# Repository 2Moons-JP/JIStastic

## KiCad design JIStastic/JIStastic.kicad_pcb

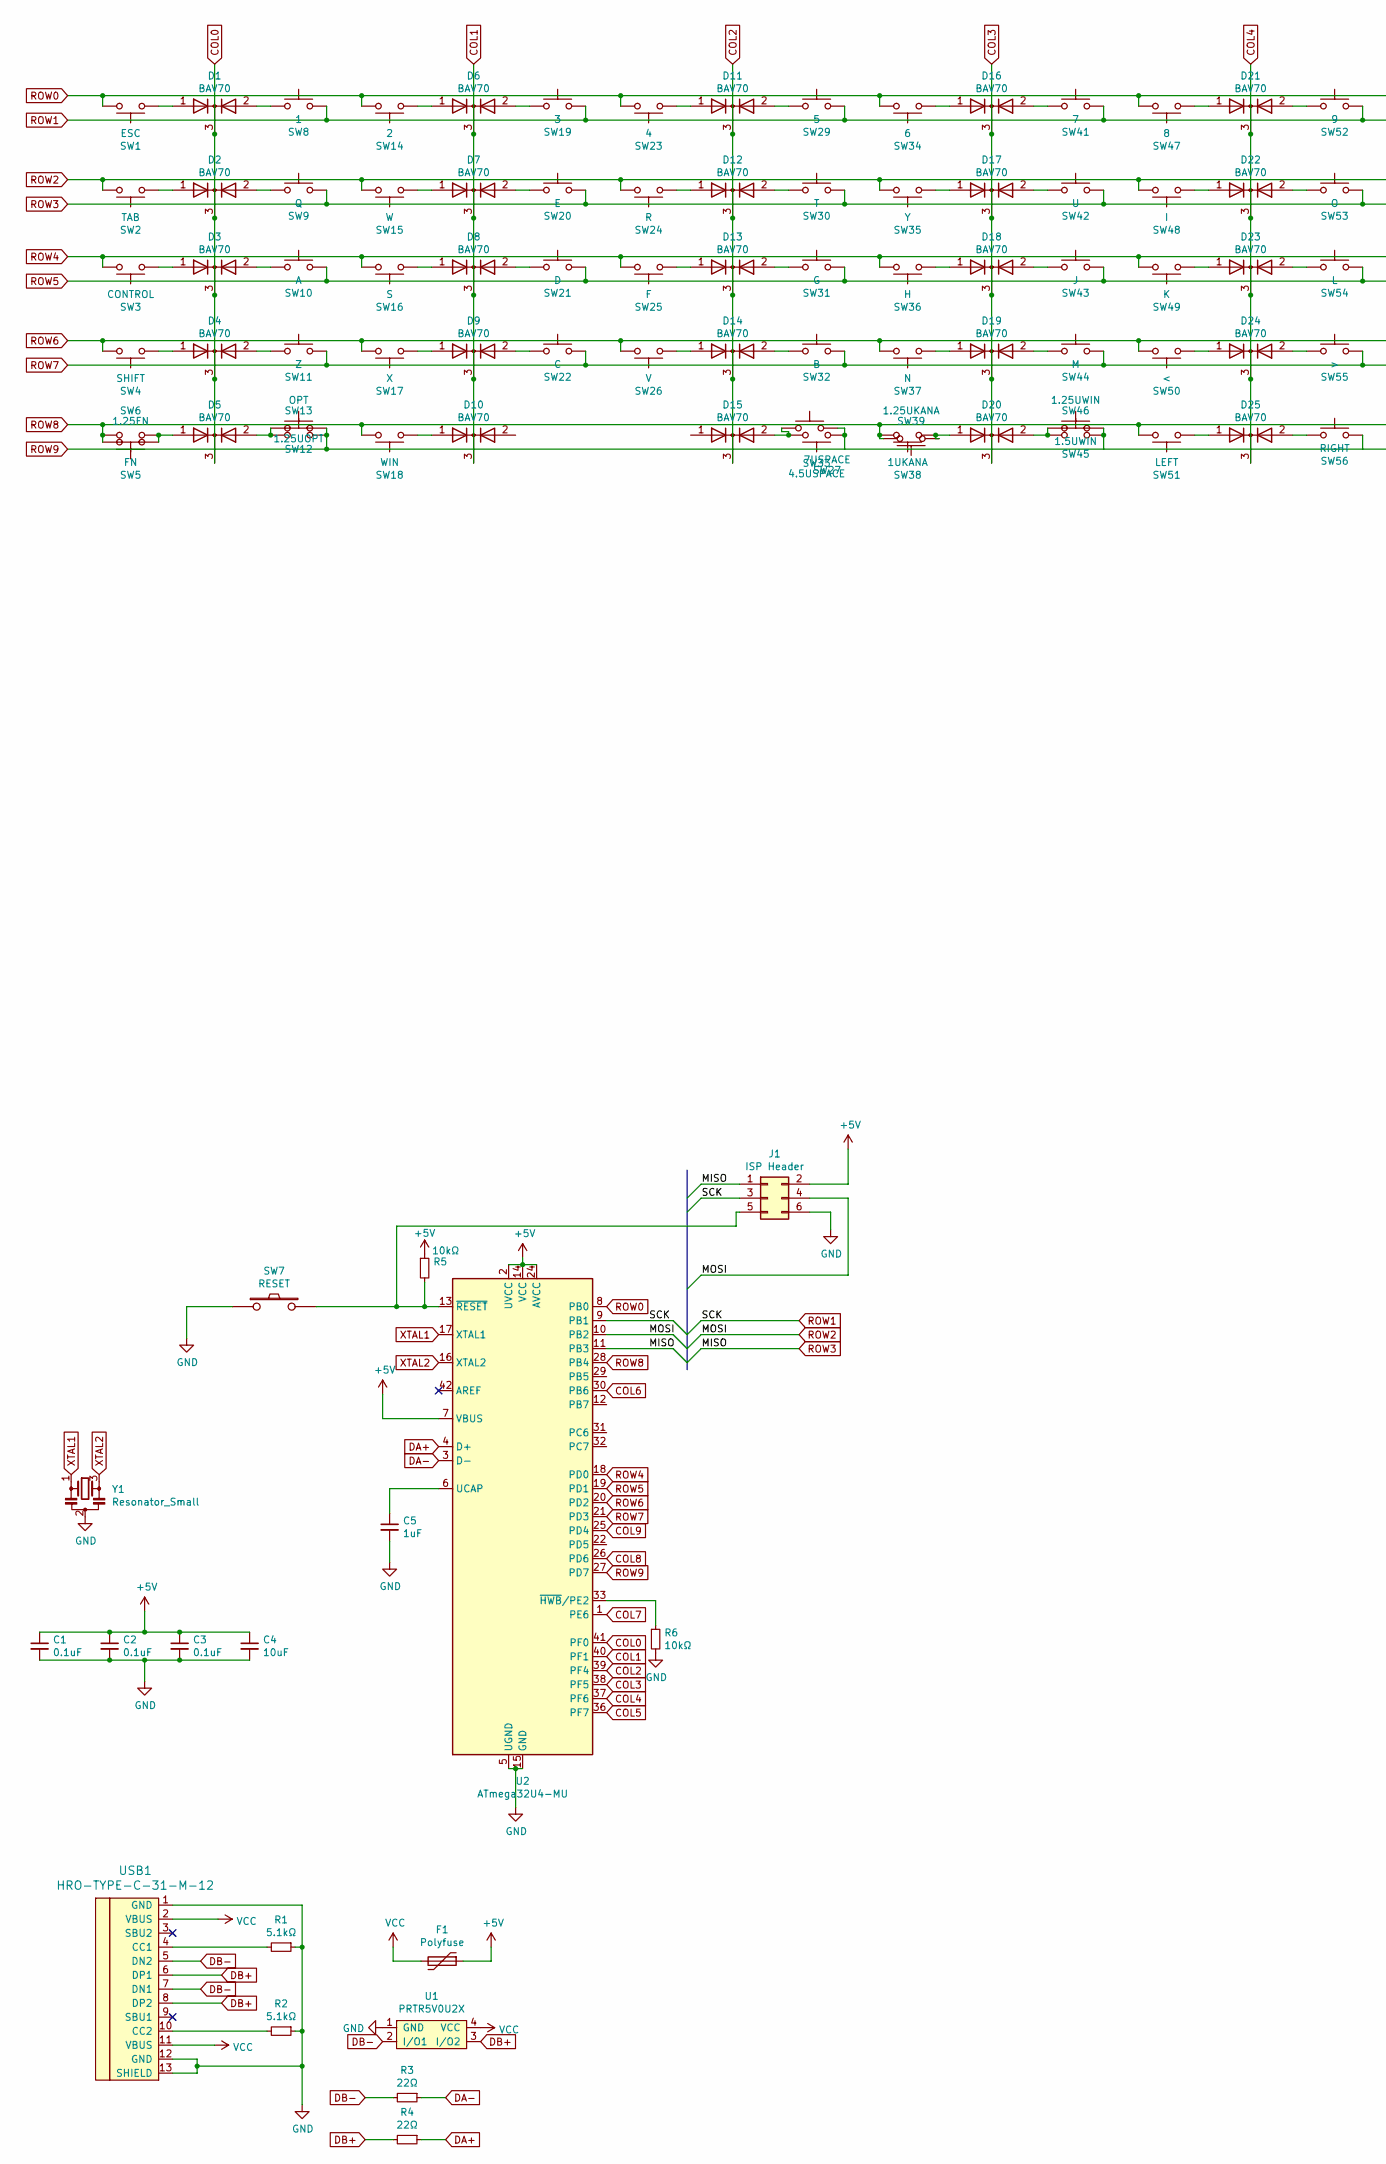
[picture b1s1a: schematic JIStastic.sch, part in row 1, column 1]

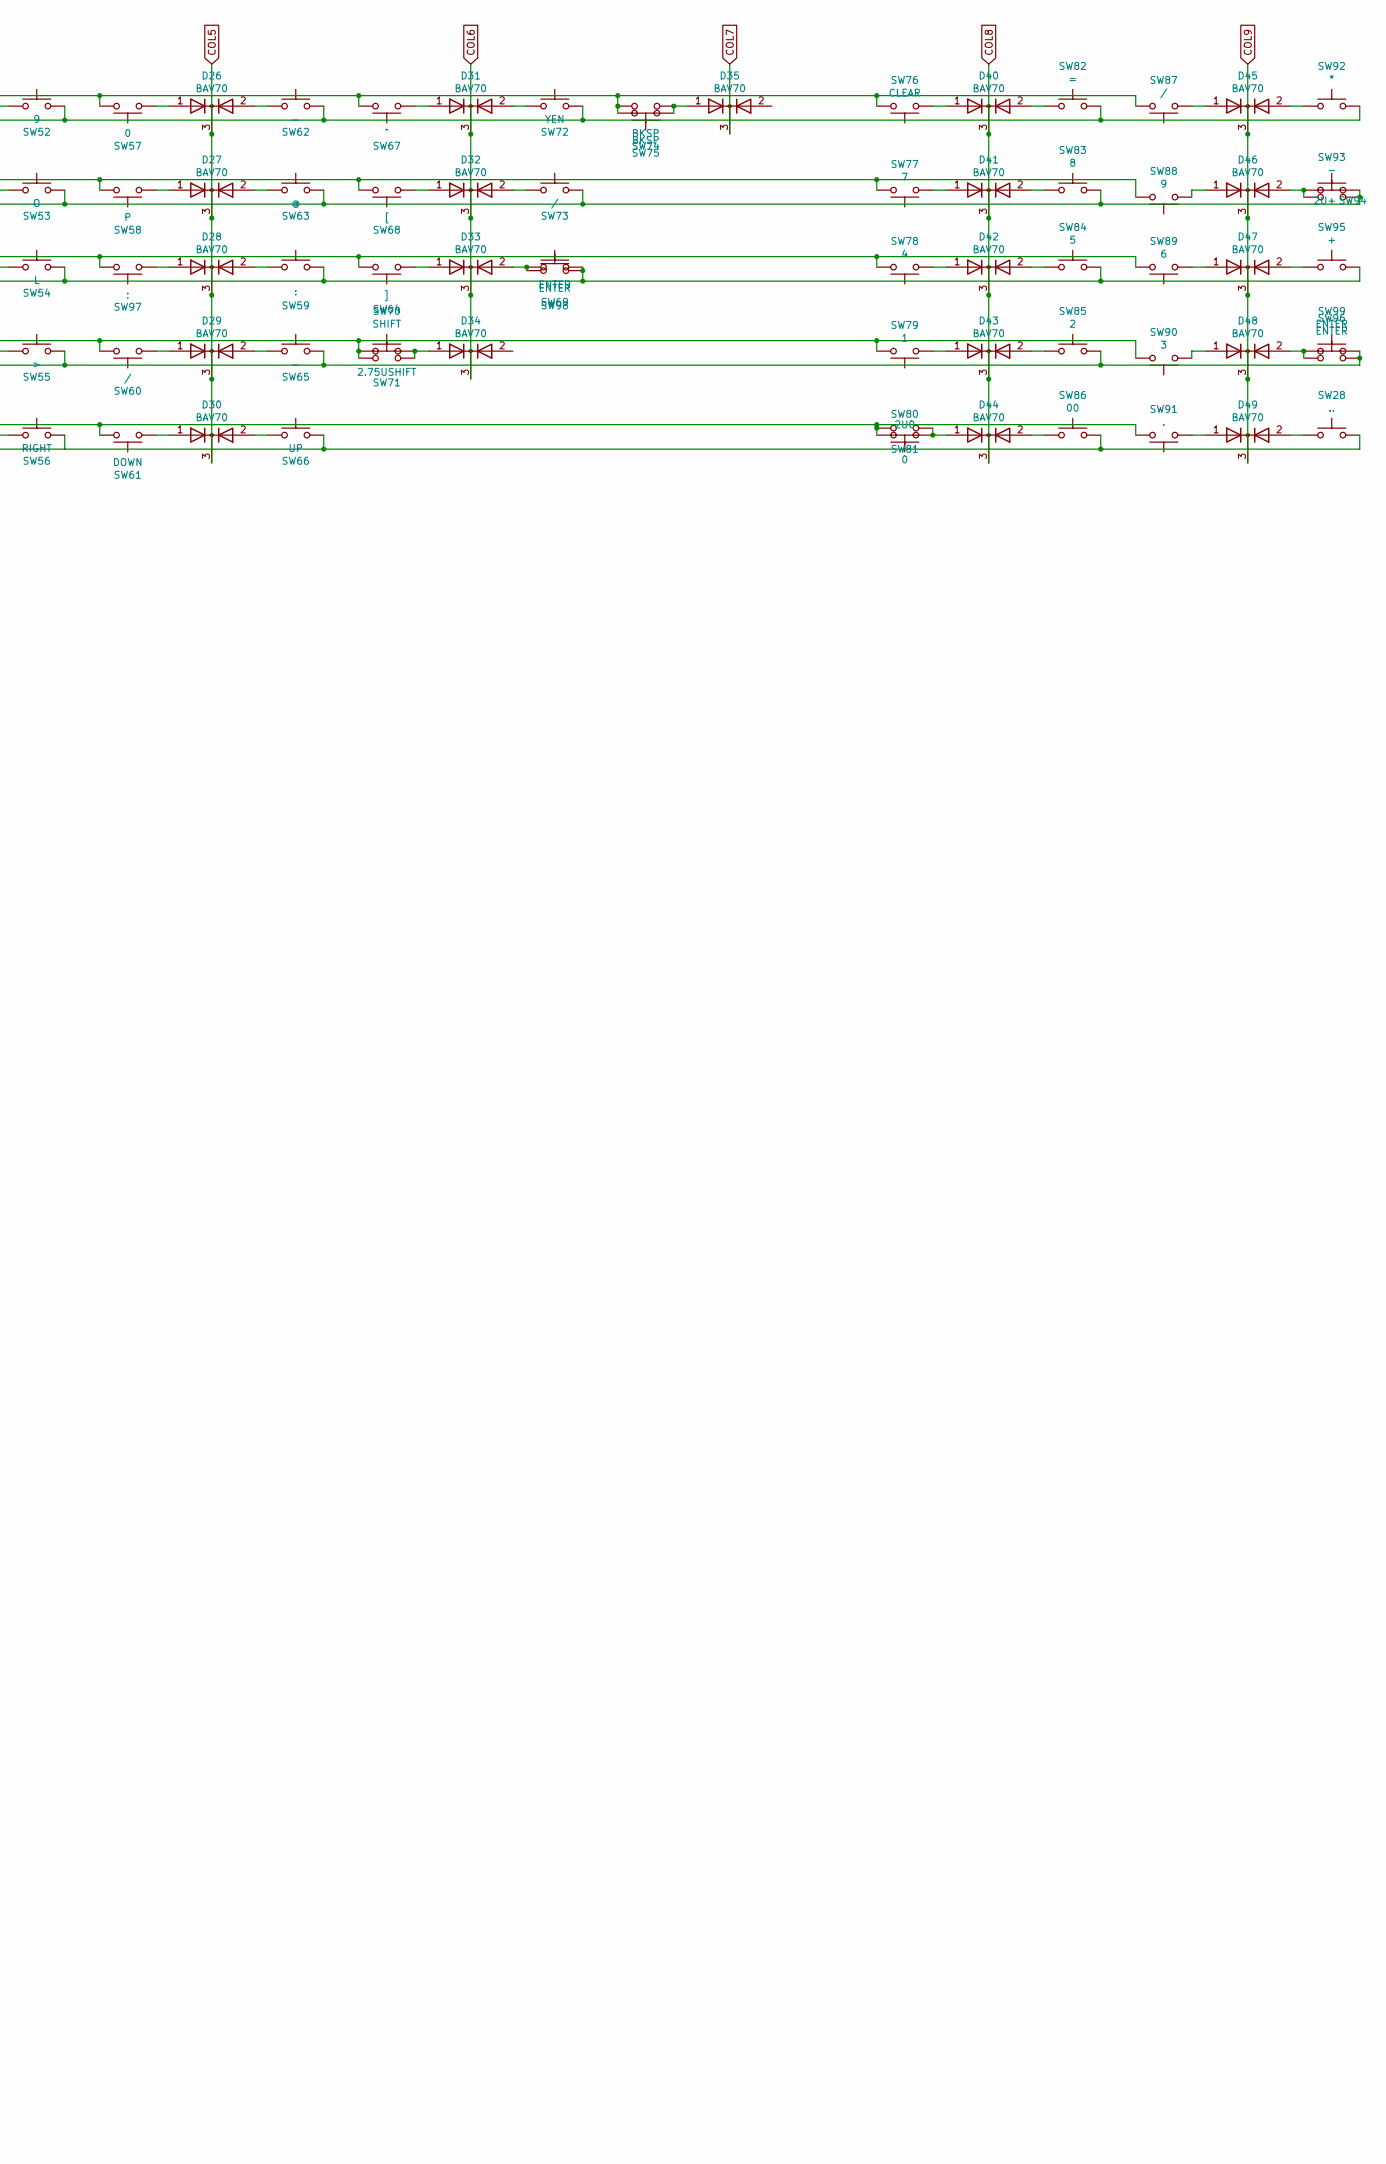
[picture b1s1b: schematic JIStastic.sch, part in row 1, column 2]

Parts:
C1, C2, C3: 0.1uF; C_0805_2012Metric; Part# CC0805KRX7R9BB104; LCSC Part# C49678
C4: 10uF; C_0805_2012Metric; Part# CL21A106KAYNNNE; LCSC Part# C15850
C5: 1uF; C_0805_2012Metric; Part# CL21B105KBFNNNE; LCSC Part# C28323
D1, D2, D3, D4, D5, D6, D7, D8, D9, D10, D11, D12, D13, D14, D15, D16, D17, D18, D19, D20, D21, D22, D23, D24, D25, D26, D27, D28, D29, D30, D31, D32, D33, D34, D35, D40, D41, D42, D43, D44, D45, D46, D47, D48, D49: BAV70; SOT-23; Part# BAV70; LCSC Part# C68978
F1: Polyfuse; Fuse_0805_2012Metric; Part# nSMD025; LCSC Part# C70068
J1: ISP Header; PinHeader_2x03_P2.54mm_Vertical
R1, R2: 5.1kΩ; R_0805_2012Metric; Part# 0805W8F5101T5E; LCSC Part# C27834
R3, R4: 22Ω; R_0805_2012Metric; Part# 0805W8F220JT5E; LCSC Part# C17561
R5, R6: 10kΩ; R_0805_2012Metric; Part# 0805W8F1002T5E; LCSC Part# C17414
SW1: ESC; MXOnly-1U-NoLED
SW2: TAB; MXOnly-1.5U-NoLED
SW3: CONTROL; MXOnly-1.75U-NoLED
SW4: SHIFT; MXOnly-2.25U-NoLED
SW5: FN; MXOnly-1U-NoLED
SW6: 1.25FN; MXOnly-1.25U-NoLED
SW7: RESET; SKQG-1155865; LCSC Part# C221929
SW8, SW79: 1; MXOnly-1U-NoLED
SW9: Q; MXOnly-1U-NoLED
SW10: A; MXOnly-1U-NoLED
SW11: Z; MXOnly-1U-NoLED
SW12: 1.25UOPT; MXOnly-1.25U-NoLED
SW13: OPT; MXOnly-1.5U-NoLED
SW14, SW85: 2; MXOnly-1U-NoLED
SW15: W; MXOnly-1U-NoLED
SW16: S; MXOnly-1U-NoLED
SW17: X; MXOnly-1U-NoLED
SW18: WIN; MXOnly-1.5U-NoLED
SW19, SW90: 3; MXOnly-1U-NoLED
SW20: E; MXOnly-1U-NoLED
SW21: D; MXOnly-1U-NoLED
SW22: C; MXOnly-1U-NoLED
SW23, SW78: 4; MXOnly-1U-NoLED
SW24: R; MXOnly-1U-NoLED
SW25: F; MXOnly-1U-NoLED
SW26: V; MXOnly-1U-NoLED
SW27: 7USPACE; MXOnly-7U-ReversedStabilizers-NoLED
SW28: ..; MXOnly-1U-NoLED
SW29, SW84: 5; MXOnly-1U-NoLED
SW30: T; MXOnly-1U-NoLED
SW31: G; MXOnly-1U-NoLED
SW32: B; MXOnly-1U-NoLED
SW33: 4.5USPACE; MX450R
SW34, SW89: 6; MXOnly-1U-NoLED
SW35: Y; MXOnly-1U-NoLED
SW36: H; MXOnly-1U-NoLED
SW37: N; MXOnly-1U-NoLED
SW38: 1UKANA; MXOnly-1U-NoLED
SW39: 1.25UKANA; MXOnly-1.25U-NoLED
SW41, SW77: 7; MXOnly-1U-NoLED
SW42: U; MXOnly-1U-NoLED
SW43: J; MXOnly-1U-NoLED
SW44: M; MXOnly-1U-NoLED
SW45: 1.5UWIN; MXOnly-1.5U-NoLED
SW46: 1.25UWIN; MXOnly-1.25U-NoLED
SW47, SW83: 8; MXOnly-1U-NoLED
SW48: I; MXOnly-1U-NoLED
SW49: K; MXOnly-1U-NoLED
SW50: <; MXOnly-1U-NoLED
SW51: LEFT; MXOnly-1U-NoLED
SW52, SW88: 9; MXOnly-1U-NoLED
SW53: O; MXOnly-1U-NoLED
SW54: L; MXOnly-1U-NoLED
SW55: >; MXOnly-1U-NoLED
SW56: RIGHT; MXOnly-1U-NoLED
SW57, SW81: 0; MXOnly-1U-NoLED
SW58: P; MXOnly-1U-NoLED
SW59: :; MXOnly-1U-NoLED
SW60, SW87: /; MXOnly-1U-NoLED
SW61: DOWN; MXOnly-1U-NoLED
SW62, SW65, SW93: -; MXOnly-1U-NoLED
SW63: @; MXOnly-1U-NoLED
SW64: ]; MXOnly-1U-NoLED
SW66: UP; MXOnly-1U-NoLED
SW67: ^; MXOnly-1U-NoLED
SW68: [; MXOnly-1U-NoLED
SW69: ENTER; MXOnly-ISO-ROTATED-ReversedStabilizers-NoLED
SW70: SHIFT; MXOnly-1.75U-NoLED
SW71: 2.75USHIFT; MXOnly-2.75U-NoLED
SW72: YEN; MXOnly-1U-NoLED
SW73: /; MXOnly-1.5U-NoLED
SW74: BKSP; MXOnly-2U-NoLED
SW75: BKSP; MXOnly-1U-NoLED
SW76: CLEAR; MXOnly-1U-NoLED
SW80: 2U0; MXOnly-2U-ReversedStabilizers-NoLED
SW82: =; MXOnly-1U-NoLED
SW86: 00; MXOnly-1U-NoLED
SW91: .; MXOnly-1U-NoLED
SW92: *; MXOnly-1U-NoLED
SW94: 2U+; MXOnly-2U-ReversedStabilizers-NoLED
SW95: +; MXOnly-1U-NoLED
SW96: ENTER; MXOnly-2U-ReversedStabilizers-NoLED
SW97: ;; MXOnly-1U-NoLED
SW98: ENTER; MXOnly-2.25U-NoLED
SW99: ENTER; MXOnly-1U-NoLED
U1: PRTR5V0U2X; SOT-143
U2: ATmega32U4-MU; QFN-44-1EP_7x7mm_P0.5mm_EP5.2x5.2mm; Part# ATMEGA32U4-MUR; LCSC Part# C45874
USB1: HRO-TYPE-C-31-M-12; HRO-TYPE-C-31-M-12-Assembly; Part# TYPE-C-31-M-12; LCSC Part# C165948
Y1: Resonator_Small; Resonator_SMD_muRata_CSTxExxV-3Pin_3.0x1.1mm_HandSoldering_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; Part# CSTNE16M0V530000R0; LCSC Part# C341521

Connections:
+5V: C1.1, C2.1, C3.1, C4.1, F1.1, J1.2, R5.1, U2.2 (UVCC), U2.7 (VBUS), U2.14 (VCC), U2.24 (AVCC), U2.34 (VCC), U2.44 (AVCC)
COL0: D1.3 (K), D2.3 (K), D3.3 (K), D4.3 (K), D5.3 (K), U2.41 (PF0)
COL1: D6.3 (K), D7.3 (K), D8.3 (K), D9.3 (K), D10.3 (K), U2.40 (PF1)
COL2: D11.3 (K), D12.3 (K), D13.3 (K), D14.3 (K), D15.3 (K), U2.39 (PF4)
COL3: D16.3 (K), D17.3 (K), D18.3 (K), D19.3 (K), D20.3 (K), U2.38 (PF5)
COL4: D21.3 (K), D22.3 (K), D23.3 (K), D24.3 (K), D25.3 (K), U2.37 (PF6)
COL5: D26.3 (K), D27.3 (K), D28.3 (K), D29.3 (K), D30.3 (K), U2.36 (PF7)
COL6: D31.3 (K), D32.3 (K), D33.3 (K), D34.3 (K), U2.30 (PB6)
COL7: D35.3 (K), U2.1 (PE6)
COL8: D40.3 (K), D41.3 (K), D42.3 (K), D43.3 (K), D44.3 (K), U2.26 (PD6)
COL9: D45.3 (K), D46.3 (K), D47.3 (K), D48.3 (K), D49.3 (K), U2.25 (PD4)
DA+: R4.1, U2.4 (D+)
DA-: R3.1, U2.3 (D-)
DB+: R4.2, U1.3 (I/O2), USB1.6 (DP1), USB1.8 (DP2)
DB-: R3.2, U1.2 (I/O1), USB1.5 (DN2), USB1.7 (DN1)
GND: C1.2, C2.2, C3.2, C4.2, C5.2, J1.6, R1.1, R2.1, R6.2, SW7.1, U1.1 (GND), U2.5 (UGND), U2.15 (GND), U2.23 (GND), U2.35 (GND), U2.43 (GND), U2.45 (GND), USB1.1 (GND), USB1.12 (GND), USB1.13 (SHIELD), Y1.2
unnamed: C5.1, U2.6 (UCAP)
unnamed: D1.1 (A), SW1.1
unnamed: D1.2 (A), SW8.1
unnamed: D2.1 (A), SW2.1
unnamed: D2.2 (A), SW9.1
unnamed: D3.1 (A), SW3.1
unnamed: D3.2 (A), SW10.1
unnamed: D4.1 (A), SW4.1
unnamed: D4.2 (A), SW11.1
unnamed: D5.1 (A), SW5.1, SW6.1
unnamed: D5.2 (A), SW12.1, SW13.1
unnamed: D6.1 (A), SW14.1
unnamed: D6.2 (A), SW19.1
unnamed: D7.1 (A), SW15.1
unnamed: D7.2 (A), SW20.1
unnamed: D8.1 (A), SW16.1
unnamed: D8.2 (A), SW21.1
unnamed: D9.1 (A), SW17.1
unnamed: D9.2 (A), SW22.1
unnamed: D10.1 (A), SW18.1
unnamed: D11.1 (A), SW23.1
unnamed: D11.2 (A), SW29.1
unnamed: D12.1 (A), SW24.1
unnamed: D12.2 (A), SW30.1
unnamed: D13.1 (A), SW25.1
unnamed: D13.2 (A), SW31.1
unnamed: D14.1 (A), SW26.1
unnamed: D14.2 (A), SW32.1
unnamed: D15.2 (A), SW27.1, SW33.2
unnamed: D16.1 (A), SW34.1
unnamed: D16.2 (A), SW41.1
unnamed: D17.1 (A), SW35.1
unnamed: D17.2 (A), SW42.1
unnamed: D18.1 (A), SW36.1
unnamed: D18.2 (A), SW43.1
unnamed: D19.1 (A), SW37.1
unnamed: D19.2 (A), SW44.1
unnamed: D20.1 (A), SW38.1, SW39.1
unnamed: D20.2 (A), SW45.1, SW46.1
unnamed: D21.1 (A), SW47.1
unnamed: D21.2 (A), SW52.1
unnamed: D22.1 (A), SW48.1
unnamed: D22.2 (A), SW53.1
unnamed: D23.1 (A), SW49.1
unnamed: D23.2 (A), SW54.1
unnamed: D24.1 (A), SW50.1
unnamed: D24.2 (A), SW55.1
unnamed: D25.1 (A), SW51.1
unnamed: D25.2 (A), SW56.1
unnamed: D26.1 (A), SW57.1
unnamed: D26.2 (A), SW62.1
unnamed: D27.1 (A), SW58.1
unnamed: D27.2 (A), SW63.1
unnamed: D28.1 (A), SW97.1
unnamed: D28.2 (A), SW59.1
unnamed: D29.1 (A), SW60.1
unnamed: D29.2 (A), SW65.1
unnamed: D30.1 (A), SW61.1
unnamed: D30.2 (A), SW66.1
unnamed: D31.1 (A), SW67.1
unnamed: D31.2 (A), SW72.1
unnamed: D32.1 (A), SW68.1
unnamed: D32.2 (A), SW73.1
unnamed: D33.1 (A), SW64.1
unnamed: D33.2 (A), SW69.1, SW98.1
unnamed: D34.1 (A), SW70.2, SW71.2
unnamed: D35.1 (A), SW74.1, SW75.1
unnamed: D40.1 (A), SW76.1
unnamed: D40.2 (A), SW82.1
unnamed: D41.1 (A), SW77.1
unnamed: D41.2 (A), SW83.1
unnamed: D42.1 (A), SW78.1
unnamed: D42.2 (A), SW84.1
unnamed: D43.1 (A), SW79.1
unnamed: D43.2 (A), SW85.1
unnamed: D44.1 (A), SW80.1, SW81.1
unnamed: D44.2 (A), SW86.1
unnamed: D45.1 (A), SW87.1
unnamed: D45.2 (A), SW92.1
unnamed: D46.1 (A), SW88.1
unnamed: D46.2 (A), SW93.1, SW94.1
unnamed: D47.1 (A), SW89.1
unnamed: D47.2 (A), SW95.1
unnamed: D48.1 (A), SW90.1
unnamed: D48.2 (A), SW96.1, SW99.1
unnamed: D49.1 (A), SW91.1
unnamed: D49.2 (A), SW28.1
unnamed: J1.5, R5.2, SW7.2, U2.13 (~RESET)
unnamed: R1.2, USB1.4 (CC1)
unnamed: R2.2, USB1.10 (CC2)
unnamed: R6.1, U2.33 (~HWB~/PE2)
ROW0: SW1.2, SW14.2, SW23.2, SW34.2, SW47.2, SW57.2, SW67.2, SW74.2, SW75.2, SW76.2, SW87.2, U2.8 (PB0)
ROW1: J1.3, SW8.2, SW19.2, SW29.2, SW41.2, SW52.2, SW62.2, SW72.2, SW82.2, SW92.2, U2.9 (PB1)
ROW2: J1.4, SW2.2, SW15.2, SW24.2, SW35.2, SW48.2, SW58.2, SW68.2, SW77.2, SW88.2, U2.10 (PB2)
ROW3: J1.1, SW9.2, SW20.2, SW30.2, SW42.2, SW53.2, SW63.2, SW73.2, SW83.2, SW93.2, SW94.2, U2.11 (PB3)
ROW4: SW3.2, SW16.2, SW25.2, SW36.2, SW49.2, SW64.2, SW78.2, SW89.2, SW97.2, U2.18 (PD0)
ROW5: SW10.2, SW21.2, SW31.2, SW43.2, SW54.2, SW59.2, SW69.2, SW84.2, SW95.2, SW98.2, U2.19 (PD1)
ROW6: SW4.2, SW17.2, SW26.2, SW37.2, SW50.2, SW60.2, SW70.1, SW71.1, SW79.2, SW90.2, U2.20 (PD2)
ROW7: SW11.2, SW22.2, SW32.2, SW44.2, SW55.2, SW65.2, SW85.2, SW96.2, SW99.2, U2.21 (PD3)
ROW8: SW5.2, SW6.2, SW18.2, SW38.2, SW39.2, SW51.2, SW61.2, SW80.2, SW81.2, SW91.2, U2.28 (PB4)
ROW9: SW12.2, SW13.2, SW27.2, SW28.2, SW33.1, SW45.2, SW46.2, SW56.2, SW66.2, SW86.2, U2.27 (PD7)
VCC: F1.2, U1.4 (VCC), USB1.2 (VBUS), USB1.11 (VBUS)
XTAL1: U2.17 (XTAL1), Y1.1
XTAL2: U2.16 (XTAL2), Y1.3

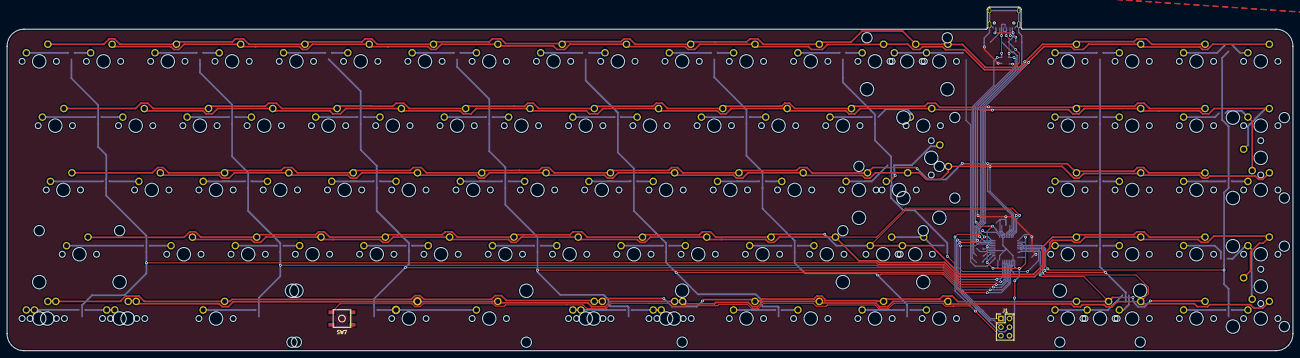
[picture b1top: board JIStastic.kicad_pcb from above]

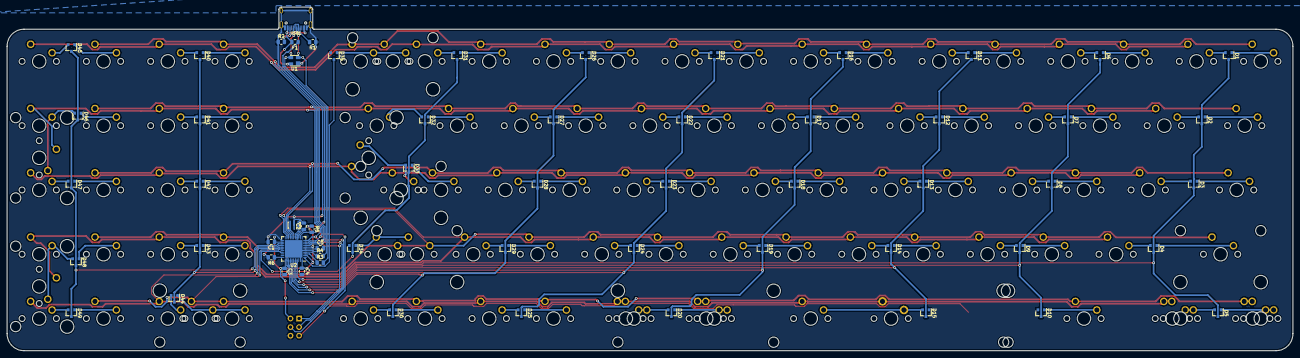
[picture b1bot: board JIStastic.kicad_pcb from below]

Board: 2 copper layers, 381.0 x 101.8 mm, 160 parts (62 on the bottom side), 120 nets.

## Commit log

2021-12-20 12/20
2021-12-21 12/21
